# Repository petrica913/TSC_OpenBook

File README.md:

# 📘 OpenBook - EBook Reader with ESP32-C6

## 📊 Block diagram

## 🧠 Detailed Hardware Description

### Microcontroller
- **ESP32-C6-WROOM-1-N8** – Main MCU with WiFi 6 and BLE 5.0 support.
- Manages all components and communication interfaces.

### Power Supply
- **USB-C Connector (J2)** – for powering and charging the device.
- **MCP73831** – LiPo battery charging IC.
- **P-Channel MOSFETs (Q1, Q2)** – for automatic switching between USB and battery power.
- **Varistor and 5.1kΩ resistors** – for overvoltage protection and USB-C detection.

### Display
- **eInk display** controlled via **SPI** interface:
  - Lines: CLK, MOSI, CS, DC (Data/Command), RST (Reset), BUSY (status).
  - Extremely power-efficient – consumes power only during screen refresh.

### User Interface
- Physical buttons for menu control:
  - Left/Right navigation and Select.
  - Connected to GPIOs configured as input, some with pull-up/down resistors.

### Sensors (optional)
- **BME680** – temperature, humidity, pressure, and VOC sensor.
  - Communicates via I2C.
  - Connected to GPIOs with 10kΩ pull-up resistors.

### Other Components
- Resistors, filtering and decoupling capacitors.
- Status LEDs (optional).

## 🔋 Estimated Power Consumption

| Component                                | Estimated Current             |
|------------------------------------------|-------------------------------|
| ESP32-C6 (CPU active, without Wi-Fi)     | ~80–120 mA                    |
| E-Paper (page refresh)                   | ~10–15 mA *(only during refresh)* |
| MicroSD (active access)                  | ~30–60 mA                     |
| RTC DS3231                               | ~0.2 mA                       |
| BME688 Sensor (1Hz)                      | ~3.7 µA                       |
| Fuel Gauge MAX17048 (active)             | ~23 µA                        |
| LDO Regulator (quiescent current)        | ~1 µA                         |
| **Total estimated (without refresh)**    | **~110–130 mA**               |
| **Total during EPD refresh**             | **~140–170 mA**               |

## 🔌 Pin Allocation of ESP32-C6

| Pin Number | GPIO | Function              | Componenta                            | Reason for Use                                   |
|------------|------|------------------------|---------------------------------------|--------------------------------------------------------|
| 3          | EN   | Reset                  | Reset Button                          | Hardware-defined enable pin                            |
| 8          | GPIO0 | SQW/INT               | RTC DS3231SN Interrupt                | Used to wakeup from sleep using an interrupt from RTC  |
| 9          | GPIO1 | 32KHz input           | RTC DS3231SN 32KHz output             | Low power timing source for RTC operations             |
| 27         | GPIO2 | MISO                  | SD Card, E-Paper, NOR Flash           | SPI MISO - receives data from connected peripherals    |
| 28         | GPIO3 | EPD_BUSY              | E-Paper Display busy signal           | Indicates the status of the E-Paper display            |
| 30         | GPIO4 | SD_CS                 | SD Card chip select                   | Selects the SD card on the SPI bus                     |
| 31         | GPIO5 | EPD_DC                | E-Paper Display data/command          | Distinguishes data/command                             |
| 32         | GPIO6 | SCK                   | SD Card, E-Paper, NOR Flash           | SPI clock line                                         |
| 33         | GPIO7 | MOSI                  | SD Card, E-Paper, NOR Flash           | SPI data line                                          |
| 10         | GPIO8 | Pull-up               | Reserved - Unused                     | Left free                                              |
| 13         | GPIO9 | Boot                  | Boot Button                           | Enter flashing mode                                    |
| 14         | GPIO10 | EPD_CS               | E-Paper Display chip select           | Selects E-Paper                                        |
| 15         | GPIO11 | FLASH_CS             | NOR Flash chip select                 | Selects external flash                                 |
| 16         | GPIO12 | USB_D-               | USB Data negative                     | USB data line                                          |
| 17         | GPIO13 | USB_D+               | USB Data positive                     | USB data line                                          |
| 23         | GPIO15 | Navigation           | Change Button                         | Input detection                                        |
| 25         | GPIO16 | TX                   | Test Pad                              | TX                                                     |
| 24         | GPIO17 | RX                   | Test Pad                              | RX                                                     |
| 16         | GPIO18 | RTC_RST              | RTC reset                             | Resets RTC module                                      |
| 17         | GPIO19 | I2C_PW               | BME688 power control                  | Powers I2C modules                                     |
| 18         | GPIO20 | EPD_3V3              | DMG2305UX-7                           | Controls power supply to E-Paper display               |
| 19         | GPIO21 | SDA                  | I2C data (RTC, BME688, Battery Gauge) | I2C data line                                          |
| 20         | GPIO22 | SCL                  | I2C clock (RTC, BME688, Battery Gauge)| I2C clock line                                         |
| 21         | GPIO23 | EPD_RST              | E-Paper Display reset                 | Resets the display                                     |

## 📋 Bill of Materials (BOM)
[The bill of materials can be found here](Manufacturing/BOM_OpenBook.csv)

## 🎬 Video of the OpenBook

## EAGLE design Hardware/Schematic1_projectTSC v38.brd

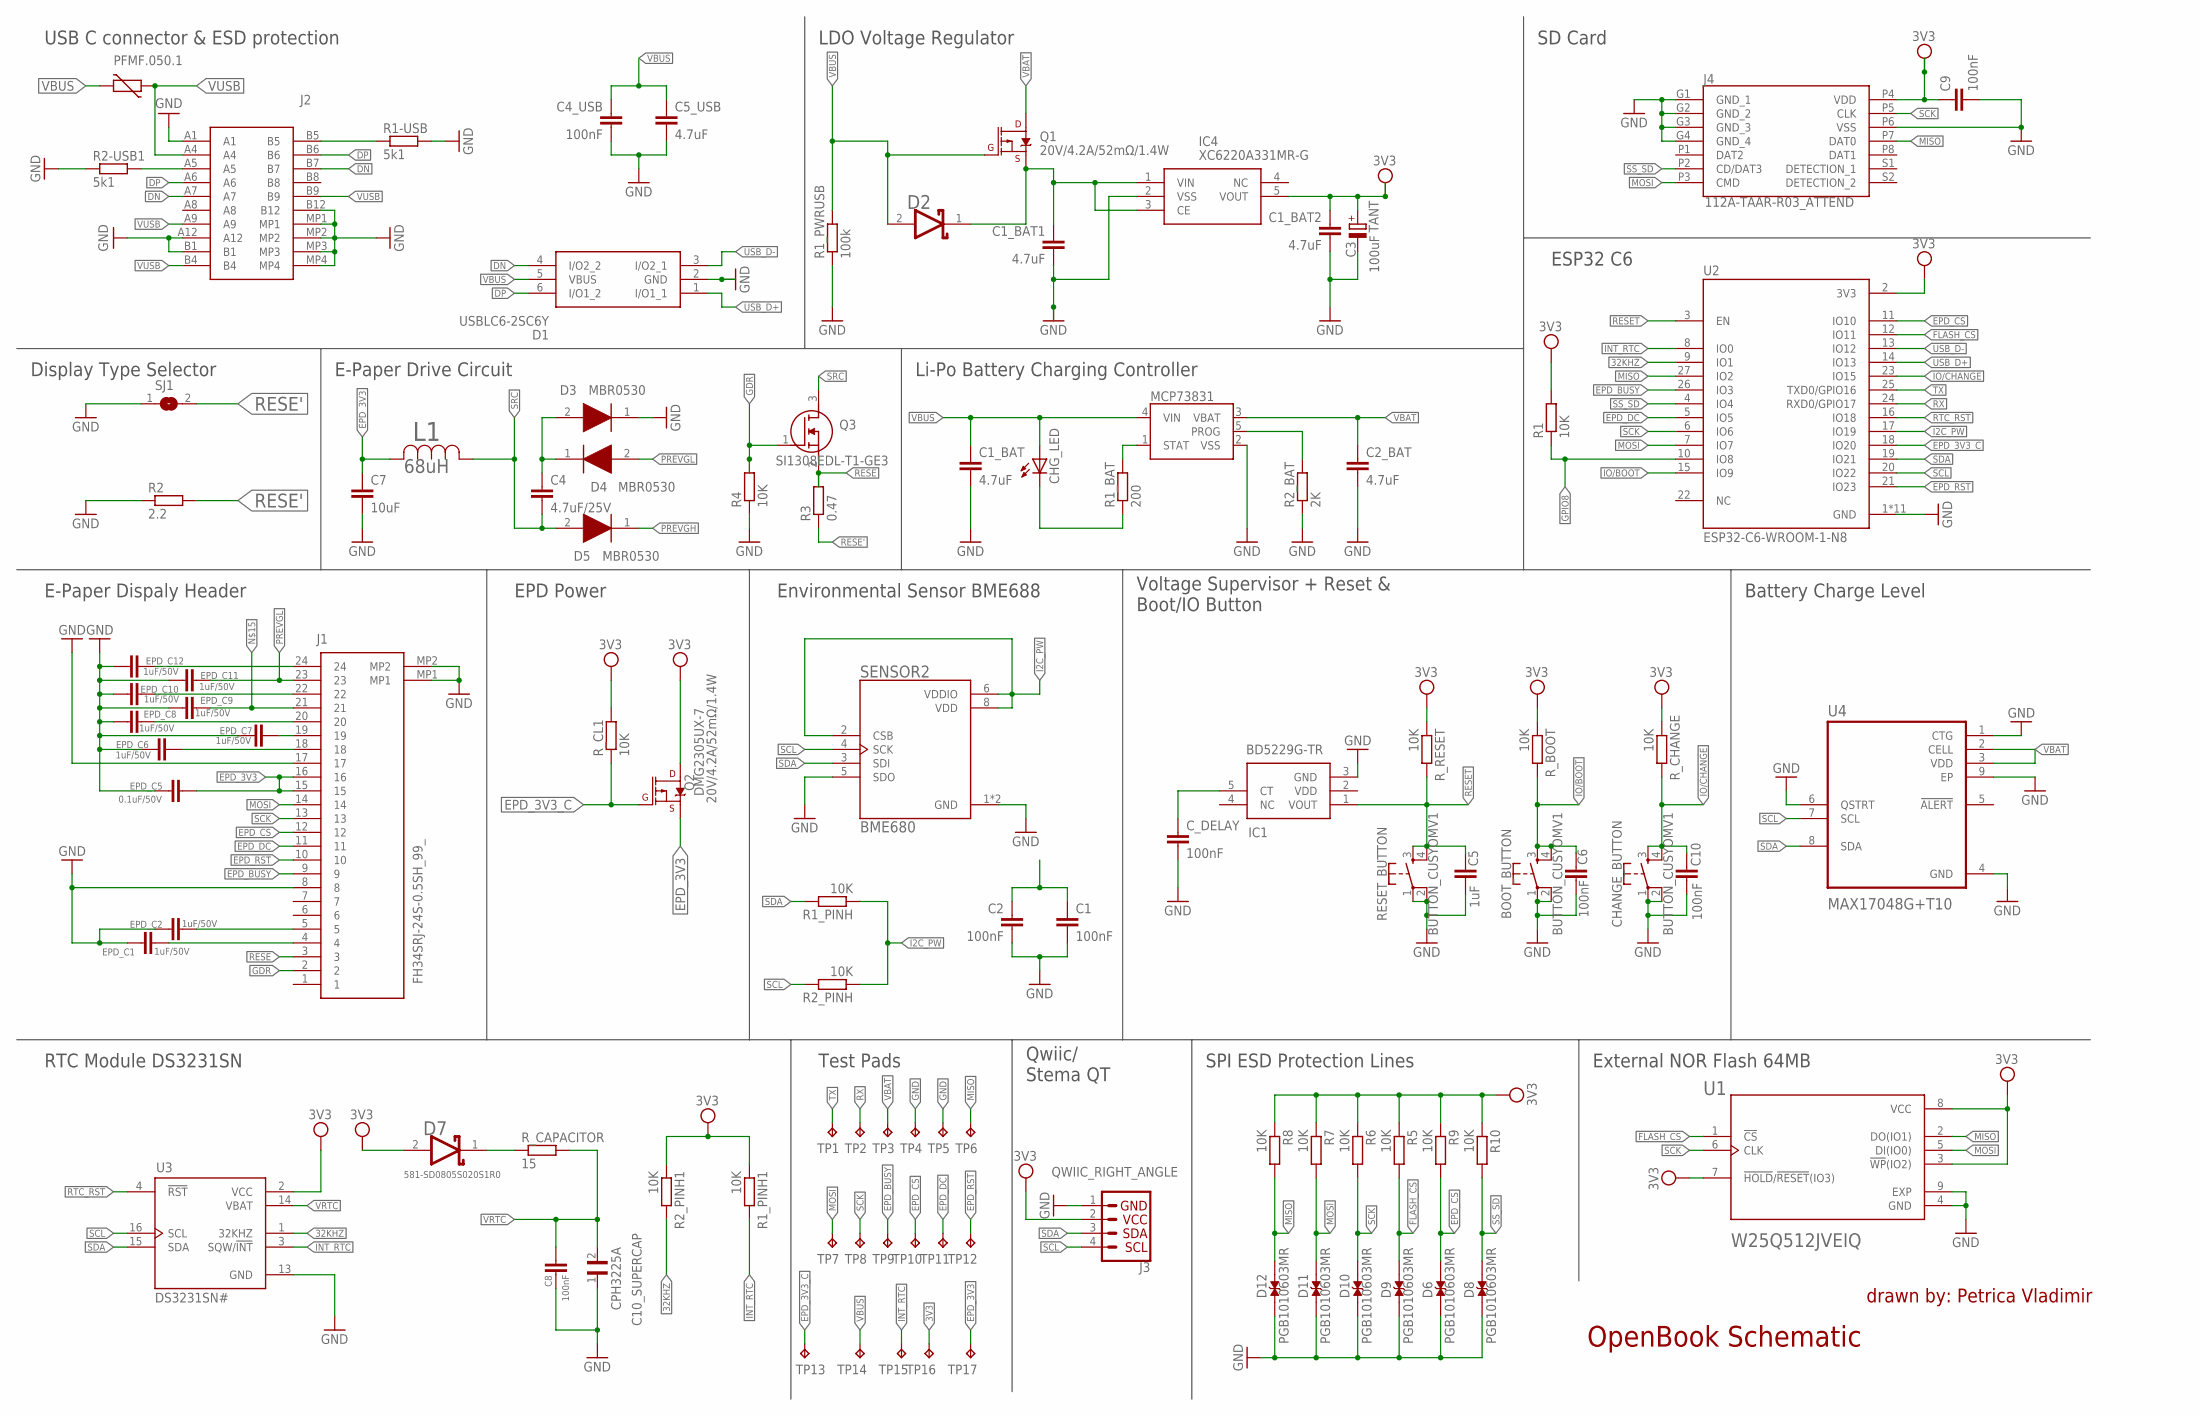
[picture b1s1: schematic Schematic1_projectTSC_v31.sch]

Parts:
BOOT_BUTTON: BUTTON_CUSYOMV1; MYBUTTON
C1, C2, C4_USB, C6, C8, C9, C10: 100nF; EAGLE-LTSPICE_C0402
C1_BAT, C1_BAT1, C1_BAT2, C2_BAT, C5_USB: 4.7uF; EAGLE-LTSPICE_C0402
C3: 100uF; RCL_CT3528
C4: 4.7uF/25V; EAGLE-LTSPICE_C0402
C5: 1uF; EAGLE-LTSPICE_C0402
C7: 10uF; EAGLE-LTSPICE_C0402
C10_SUPERCAP: CPH3225A; CAPCP3225X100N
CHANGE_BUTTON: BUTTON_CUSYOMV1; MYBUTTON
CHG_LED: ADAFRUIT_LEDCHIP-LED0603; ADAFRUIT_CHIP-LED0603
C_DELAY: 100nF; EAGLE-LTSPICE_C0402
D1: USBLC6-2SC6Y; SOT95P280X145-6N
D2, D7: ESP32_WROVER_AVX---SD0805S020S1R0_AVX_SD0805S020S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; ESP32_WROVER_AVX---SD0805S020S1R0_AVX_SD0805S020S1R0_0
D3, D4, D5: MBR0530; SOD3716X135N
D6, D8, D9, D10, D11, D12: PGB1010603MR; DIOC1608X36N
EPD_C1, EPD_C2, EPD_C6, EPD_C7, EPD_C8, EPD_C9, EPD_C10, EPD_C11, EPD_C12: 1uF/50V; EAGLE-LTSPICE_C0402
EPD_C5: 0.1uF/50V; EAGLE-LTSPICE_C0402
IC1: BD5229G-TR; SOT95P280X125-5N
IC4: XC6220A331MR-G; SOT95P280X120-5N
J1: FH34SRJ-24S-0.5SH_99_; FH34SRJ24S05SH99
J2: SAMACSYS_PARTS_USB4110-GF-A; SAMACSYS_PARTS_USB4110GFA
J3: QWIIC_RIGHT_ANGLE; JST04_1MM_RA
J4: 112A-TAAR-R03_ATTEND; 112ATAARR03ATTEND
L1: 744043680IND_4828-WE-TPC_WRE; IND_4828-WE-TPC_WRE; MANUFACTURER_PART_NUMBER 68uH
MCP73831: ESP32_WROVER_SPARKFUN-IC-POWER_MCP73831; ESP32_WROVER_SPARKFUN-IC-POWER_SOT23-5
PFMF.050.1: ESP32C6_VARISTORCN1812; ESP32C6_VARISTOR_CT/CN1812
Q1, Q2: 20V/4.2A/52mΩ/1.4W; ESP32_WROVER_SPARKFUN-DISCRETESEMI_SOT23-3
Q3: SI1308EDL-T1-GE3; SOT65P210X110-3N
R1, R1_PINH, R1_PINH1, R2_PINH, R2_PINH1, R4, R5, R6, R7, R8, R9, R10: 10K; ESP32_WROVER_EAGLE-LTSPICE_R0402
R1-USB, R2-USB1: 5k1; ESP32_WROVER_EAGLE-LTSPICE_R0402
R1_BAT: 200; ESP32_WROVER_EAGLE-LTSPICE_R0402
R1_PWRUSB: 100k; ESP32_WROVER_EAGLE-LTSPICE_R0402
R2: 2.2; ESP32_WROVER_EAGLE-LTSPICE_R0402
R2_BAT: 2K; ESP32_WROVER_EAGLE-LTSPICE_R0402
R3: 0.47; ESP32_WROVER_EAGLE-LTSPICE_R0402
RESET_BUTTON: BUTTON_CUSYOMV1; MYBUTTON
R_BOOT: 10K; ESP32_WROVER_EAGLE-LTSPICE_R0402
R_CAPACITOR: 15; ESP32_WROVER_EAGLE-LTSPICE_R0402
R_CHANGE: 10K; ESP32_WROVER_EAGLE-LTSPICE_R0402
R_CL1: 10K; ESP32_WROVER_EAGLE-LTSPICE_R0402
R_RESET: 10K; ESP32_WROVER_EAGLE-LTSPICE_R0402
SENSOR2: ESP32_WROVER_BME680_BME680; ESP32_WROVER_BME680_PSON80P300X300X100-8N
SJ1: SJ
TP1, TP2, TP3, TP4, TP5, TP6, TP7, TP8, TP9, TP10, TP11, TP12, TP13, TP14, TP15, TP16, TP17: TPTP20R; TP20R
U1: W25Q512JVEIQ; SON127P600X800X80-9N
U2: ESP32-C6-WROOM-1-N8; XCVR_ESP32-C6-WROOM-1-N8
U3: DS3231SN#; SOIC127P1032X265-16N
U4: MAX17048G+T10; SON50P200X200X80-9N

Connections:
3V3: C1_BAT2.1, C3.+, C9.1, D7.2 (ANODE), IC4.5 (VOUT), J3.2, J4.P4 (VDD), Q2.3 (D), R1.2, R1_PINH1.1, R2_PINH1.1, R5.1, R6.1, R7.1, R8.1, R9.1, R10.1, R_BOOT.1, R_CHANGE.1, R_CL1.2, R_RESET.1, TP16.TP, U1.3 (!WP!(IO2)), U1.7 (!HOLD!/!RESET!(IO3)), U1.8 (VCC), U2.2 (3V3), U3.2 (VCC)
32KHZ: R2_PINH1.2, U2.9 (IO1), U3.1 (32KHZ)
DN: D1.4 (I/O2_2), J2.A7, J2.B7
DP: D1.6 (I/O1_2), J2.A6, J2.B6
EPD_3V3_C: Q2.1 (G), R_CL1.1, TP13.TP, U2.18 (IO20)
EPD_BUSY: J1.9, TP9.TP, U2.26 (IO3)
EPD_CS: D6.2, J1.12, R9.2, TP10.TP, U2.11 (IO10)
EPD_DC: J1.11, TP11.TP, U2.5 (IO5)
EPD_RST: J1.10, TP12.TP, U2.21 (IO23)
FLASH_CS: D9.2, R5.2, U1.1 (!CS), U2.12 (IO11)
GDR: J1.2, Q3.1 (G), R4.2
GPIO8: R1.1, U2.10 (IO8)
I2C_PW: R1_PINH.1, R2_PINH.1, SENSOR2.2 (CSB), SENSOR2.6 (VDDIO), SENSOR2.8 (VDD), U2.17 (IO19)
INT_RTC: R1_PINH1.2, TP15.TP, U2.8 (IO0), U3.3 (SQW/!INT)
IO/BOOT: BOOT_BUTTON.3, BOOT_BUTTON.4, C6.1, R_BOOT.2, U2.15 (IO9)
IO/CHANGE: C10.1, CHANGE_BUTTON.3, CHANGE_BUTTON.4, R_CHANGE.2, U2.23 (IO15)
MISO: D12.2, J4.P7 (DAT0), R8.2, TP6.TP, U1.2 (DO(IO1)), U2.27 (IO2)
MOSI: D11.2, J1.14, J4.P3 (CMD), R7.2, TP7.TP, U1.5 (DI(IO0)), U2.7 (IO7)
unnamed: J2.A5, R2-USB1.2
unnamed: J2.B5, R1-USB.1
unnamed: MCP73831.1 (STAT), R1_BAT.2
unnamed: C1_BAT1.1, D2.1 (CATHODE), IC4.1 (VIN), IC4.3 (CE), Q1.2 (S)
unnamed: CHG_LED.C, R1_BAT.1
unnamed: C4.1, D3.2 (A), D4.1 (K)
unnamed: MCP73831.5 (PROG), R2_BAT.2
unnamed: EPD_C2.2, J1.5
unnamed: EPD_C8.2, J1.20
unnamed: EPD_C12.2, J1.24
unnamed: EPD_C1.2, J1.4
unnamed: EPD_C10.2, J1.22
unnamed: C_DELAY.1, IC1.5 (CT)
unnamed: D7.1 (CATHODE), R_CAPACITOR.1
unnamed: EPD_C7.2, J1.19
unnamed: EPD_C6.2, J1.18
PREVGL: D4.2 (A), EPD_C11.2, J1.23
RESE: J1.3, Q3.2 (S), R3.2
RESE': R2.2, R3.1, SJ1.2
RESET: C5.1, IC1.1 (VOUT), RESET_BUTTON.3, RESET_BUTTON.4, R_RESET.2, U2.3 (EN)
RTC_RST: U2.16 (IO18), U3.4 (!RST)
RX: TP2.TP, U2.24 (RXD0/GPIO17)
SCK: D10.2, J1.13, J4.P5 (CLK), R6.2, TP8.TP, U1.6 (CLK), U2.6 (IO6)
SCL: J3.4, R2_PINH.2, SENSOR2.4 (SCK), U2.20 (IO22), U3.16 (SCL), U4.7 (SCL)
SDA: J3.3, R1_PINH.2, SENSOR2.3 (SDI), U2.19 (IO21), U3.15 (SDA), U4.8 (SDA)
SRC: C4.2, D5.2 (A), L1.1, Q3.3 (D)
SS_SD: D8.2, J4.P2 (CD/DAT3), R10.2, U2.4 (IO4)
TX: TP1.TP, U2.25 (TXD0/GPIO16)
USB_D+: D1.1 (I/O1_1), U2.14 (IO13)
USB_D-: D1.3 (I/O2_1), U2.13 (IO12)
VBAT: C2_BAT.1, MCP73831.3 (VBAT), Q1.3 (D), TP3.TP, U4.2 (CELL), U4.3 (VDD)
VBUS1: C1.1, C2.1
VRTC: C8.2, C10_SUPERCAP.2, R_CAPACITOR.2, U3.14 (VBAT)

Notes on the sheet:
USB C connector & ESD protection
SD Card
LDO Voltage Regulator
Display Type Selector
E-Paper Drive Circuit
Li-Po Battery Charging Controller
ESP32 C6
E-Paper Dispaly Header
EPD Power
Environmental Sensor BME688
Voltage Supervisor + Reset & Boot/IO Button
Battery Charge Level
RTC Module DS3231SN
Test Pads
Qwiic/ Stema QT
SPI ESD Protection Lines
External NOR Flash 64MB
OpenBook Schematic
drawn by: Petrica Vladimir

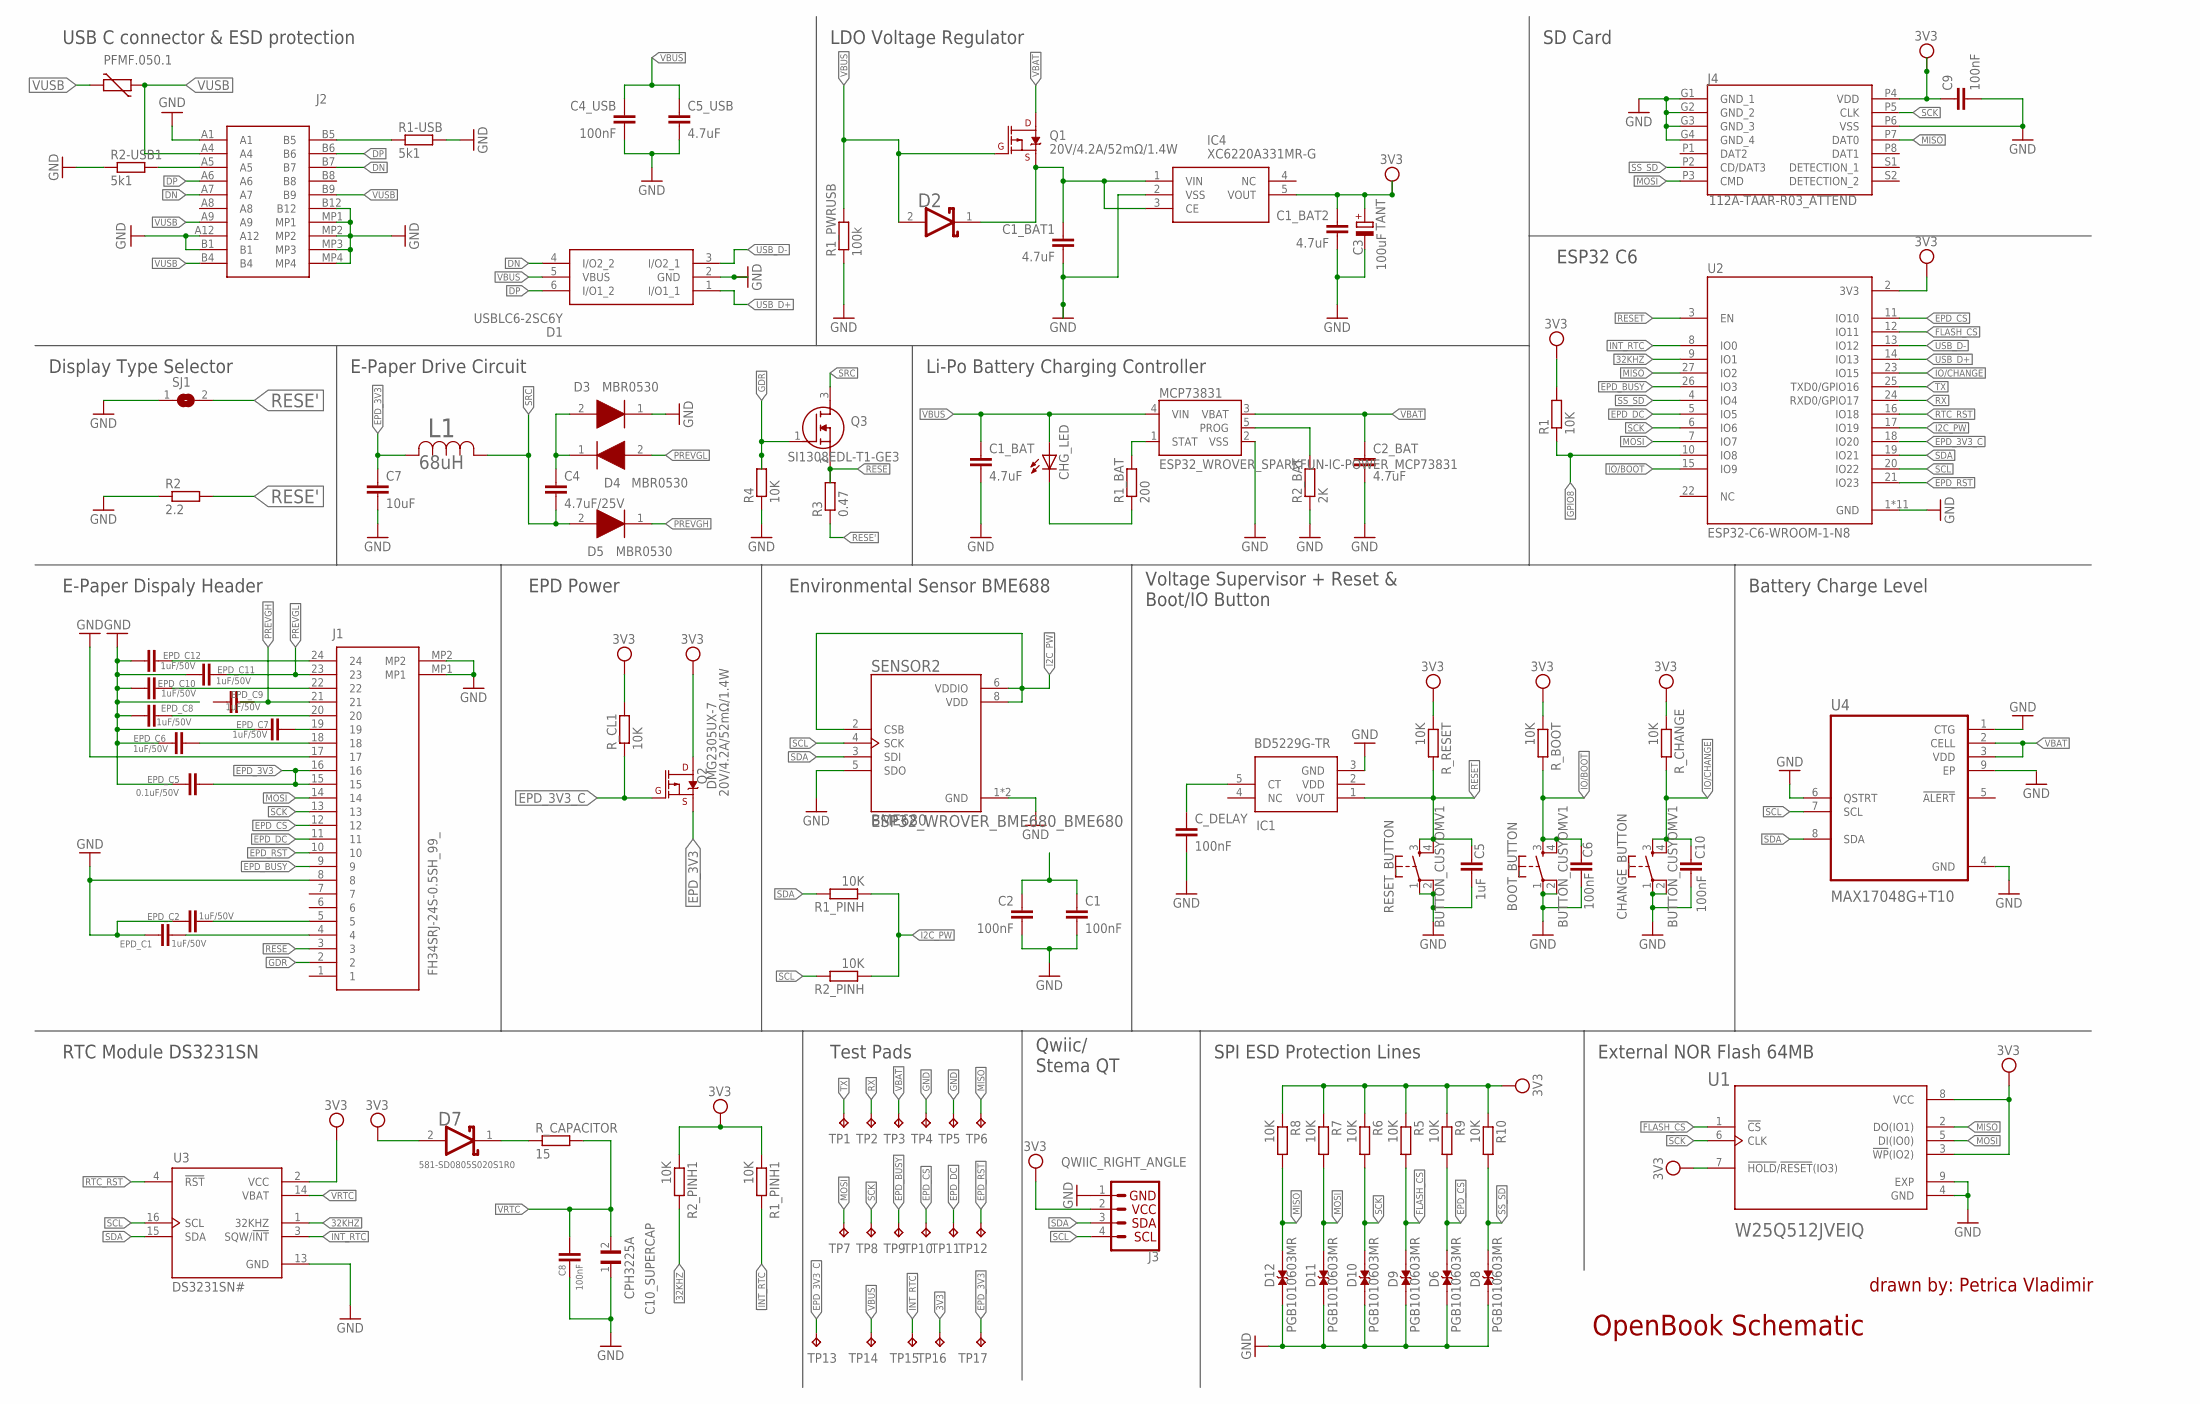
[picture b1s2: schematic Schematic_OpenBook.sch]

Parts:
BOOT_BUTTON: BUTTON_CUSYOMV1; MYBUTTON
C1, C2, C4_USB, C6, C8, C9, C10: 100nF; EAGLE-LTSPICE_C0402
C1_BAT, C1_BAT1, C1_BAT2, C2_BAT, C5_USB: 4.7uF; EAGLE-LTSPICE_C0402
C3: 100uF; RCL_CT3528
C4: 4.7uF/25V; EAGLE-LTSPICE_C0402
C5: 1uF; EAGLE-LTSPICE_C0402
C7: 10uF; EAGLE-LTSPICE_C0402
C10_SUPERCAP: CPH3225A; CAPCP3225X100N
CHANGE_BUTTON: BUTTON_CUSYOMV1; MYBUTTON
CHG_LED: ADAFRUIT_LEDCHIP-LED0603; ADAFRUIT_CHIP-LED0603
C_DELAY: 100nF; EAGLE-LTSPICE_C0402
D1: USBLC6-2SC6Y; SOT95P280X145-6N
D2, D7: ESP32_WROVER_AVX---SD0805S020S1R0_AVX_SD0805S020S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; ESP32_WROVER_AVX---SD0805S020S1R0_AVX_SD0805S020S1R0_0
D3, D4, D5: MBR0530; SOD3716X135N
D6, D8, D9, D10, D11, D12: PGB1010603MR; DIOC1608X36N
EPD_C1, EPD_C2, EPD_C6, EPD_C7, EPD_C8, EPD_C9, EPD_C10, EPD_C11, EPD_C12: 1uF/50V; EAGLE-LTSPICE_C0402
EPD_C5: 0.1uF/50V; EAGLE-LTSPICE_C0402
IC1: BD5229G-TR; SOT95P280X125-5N
IC4: XC6220A331MR-G; SOT95P280X120-5N
J1: FH34SRJ-24S-0.5SH_99_; FH34SRJ24S05SH99
J2: SAMACSYS_PARTS_USB4110-GF-A; SAMACSYS_PARTS_USB4110GFA
J3: QWIIC_RIGHT_ANGLE; JST04_1MM_RA
J4: 112A-TAAR-R03_ATTEND; 112ATAARR03ATTEND
L1: 744043680IND_4828-WE-TPC_WRE; IND_4828-WE-TPC_WRE; MANUFACTURER_PART_NUMBER 68uH
MCP73831: ESP32_WROVER_SPARKFUN-IC-POWER_MCP73831; ESP32_WROVER_SPARKFUN-IC-POWER_SOT23-5
PFMF.050.1: ESP32C6_VARISTORCN1812; ESP32C6_VARISTOR_CT/CN1812
Q1, Q2: 20V/4.2A/52mΩ/1.4W; ESP32_WROVER_SPARKFUN-DISCRETESEMI_SOT23-3
Q3: SI1308EDL-T1-GE3; SOT65P210X110-3N
R1, R1_PINH, R1_PINH1, R2_PINH, R2_PINH1, R4, R5, R6, R7, R8, R9, R10: 10K; ESP32_WROVER_EAGLE-LTSPICE_R0402
R1-USB, R2-USB1: 5k1; ESP32_WROVER_EAGLE-LTSPICE_R0402
R1_BAT: 200; ESP32_WROVER_EAGLE-LTSPICE_R0402
R1_PWRUSB: 100k; ESP32_WROVER_EAGLE-LTSPICE_R0402
R2: 2.2; ESP32_WROVER_EAGLE-LTSPICE_R0402
R2_BAT: 2K; ESP32_WROVER_EAGLE-LTSPICE_R0402
R3: 0.47; ESP32_WROVER_EAGLE-LTSPICE_R0402
RESET_BUTTON: BUTTON_CUSYOMV1; MYBUTTON
R_BOOT: 10K; ESP32_WROVER_EAGLE-LTSPICE_R0402
R_CAPACITOR: 15; ESP32_WROVER_EAGLE-LTSPICE_R0402
R_CHANGE: 10K; ESP32_WROVER_EAGLE-LTSPICE_R0402
R_CL1: 10K; ESP32_WROVER_EAGLE-LTSPICE_R0402
R_RESET: 10K; ESP32_WROVER_EAGLE-LTSPICE_R0402
SENSOR2: ESP32_WROVER_BME680_BME680; ESP32_WROVER_BME680_PSON80P300X300X100-8N
SJ1: SJ
TP1, TP2, TP3, TP4, TP5, TP6, TP7, TP8, TP9, TP10, TP11, TP12, TP13, TP14, TP15, TP16, TP17: TPTP20R; TP20R
U1: W25Q512JVEIQ; SON127P600X800X80-9N
U2: ESP32-C6-WROOM-1-N8; XCVR_ESP32-C6-WROOM-1-N8
U3: DS3231SN#; SOIC127P1032X265-16N
U4: MAX17048G+T10; SON50P200X200X80-9N

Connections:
3V3: C1_BAT2.1, C3.+, C9.1, D7.2 (ANODE), IC4.5 (VOUT), J3.2, J4.P4 (VDD), Q2.3 (D), R1.2, R1_PINH1.1, R2_PINH1.1, R5.1, R6.1, R7.1, R8.1, R9.1, R10.1, R_BOOT.1, R_CHANGE.1, R_CL1.2, R_RESET.1, TP16.TP, U1.3 (!WP!(IO2)), U1.7 (!HOLD!/!RESET!(IO3)), U1.8 (VCC), U2.2 (3V3), U3.2 (VCC)
32KHZ: R2_PINH1.2, U2.9 (IO1), U3.1 (32KHZ)
DN: D1.4 (I/O2_2), J2.A7, J2.B7
DP: D1.6 (I/O1_2), J2.A6, J2.B6
EPD_3V3_C: Q2.1 (G), R_CL1.1, TP13.TP, U2.18 (IO20)
EPD_BUSY: J1.9, TP9.TP, U2.26 (IO3)
EPD_CS: D6.2, J1.12, R9.2, TP10.TP, U2.11 (IO10)
EPD_DC: J1.11, TP11.TP, U2.5 (IO5)
EPD_RST: J1.10, TP12.TP, U2.21 (IO23)
FLASH_CS: D9.2, R5.2, U1.1 (!CS), U2.12 (IO11)
GDR: J1.2, Q3.1 (G), R4.2
GPIO8: R1.1, U2.10 (IO8)
I2C_PW: R1_PINH.1, R2_PINH.1, SENSOR2.2 (CSB), SENSOR2.6 (VDDIO), SENSOR2.8 (VDD), U2.17 (IO19)
INT_RTC: R1_PINH1.2, TP15.TP, U2.8 (IO0), U3.3 (SQW/!INT)
IO/BOOT: BOOT_BUTTON.3, BOOT_BUTTON.4, C6.1, R_BOOT.2, U2.15 (IO9)
IO/CHANGE: C10.1, CHANGE_BUTTON.3, CHANGE_BUTTON.4, R_CHANGE.2, U2.23 (IO15)
MISO: D12.2, J4.P7 (DAT0), R8.2, TP6.TP, U1.2 (DO(IO1)), U2.27 (IO2)
MOSI: D11.2, J1.14, J4.P3 (CMD), R7.2, TP7.TP, U1.5 (DI(IO0)), U2.7 (IO7)
unnamed: J2.A5, R2-USB1.2
unnamed: J2.B5, R1-USB.1
unnamed: MCP73831.1 (STAT), R1_BAT.2
unnamed: C1_BAT1.1, D2.1 (CATHODE), IC4.1 (VIN), IC4.3 (CE), Q1.2 (S)
unnamed: CHG_LED.C, R1_BAT.1
unnamed: C4.1, D3.2 (A), D4.1 (K)
unnamed: MCP73831.5 (PROG), R2_BAT.2
unnamed: EPD_C2.2, J1.5
unnamed: EPD_C8.2, J1.20
unnamed: EPD_C12.2, J1.24
unnamed: EPD_C1.2, J1.4
unnamed: EPD_C10.2, J1.22
unnamed: C_DELAY.1, IC1.5 (CT)
unnamed: D7.1 (CATHODE), R_CAPACITOR.1
unnamed: EPD_C7.2, J1.19
unnamed: EPD_C6.2, J1.18
PREVGL: D4.2 (A), EPD_C11.2, J1.23
RESE: J1.3, Q3.2 (S), R3.2
RESE': R2.2, R3.1, SJ1.2
RESET: C5.1, IC1.1 (VOUT), RESET_BUTTON.3, RESET_BUTTON.4, R_RESET.2, U2.3 (EN)
RTC_RST: U2.16 (IO18), U3.4 (!RST)
RX: TP2.TP, U2.24 (RXD0/GPIO17)
SCK: D10.2, J1.13, J4.P5 (CLK), R6.2, TP8.TP, U1.6 (CLK), U2.6 (IO6)
SCL: J3.4, R2_PINH.2, SENSOR2.4 (SCK), U2.20 (IO22), U3.16 (SCL), U4.7 (SCL)
SDA: J3.3, R1_PINH.2, SENSOR2.3 (SDI), U2.19 (IO21), U3.15 (SDA), U4.8 (SDA)
SRC: C4.2, D5.2 (A), L1.1, Q3.3 (D)
SS_SD: D8.2, J4.P2 (CD/DAT3), R10.2, U2.4 (IO4)
TX: TP1.TP, U2.25 (TXD0/GPIO16)
USB_D+: D1.1 (I/O1_1), U2.14 (IO13)
USB_D-: D1.3 (I/O2_1), U2.13 (IO12)
VBAT: C2_BAT.1, MCP73831.3 (VBAT), Q1.3 (D), TP3.TP, U4.2 (CELL), U4.3 (VDD)
VBUS1: C1.1, C2.1
VRTC: C8.2, C10_SUPERCAP.2, R_CAPACITOR.2, U3.14 (VBAT)

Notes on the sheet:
USB C connector & ESD protection
SD Card
LDO Voltage Regulator
Display Type Selector
E-Paper Drive Circuit
Li-Po Battery Charging Controller
ESP32 C6
E-Paper Dispaly Header
EPD Power
Environmental Sensor BME688
Voltage Supervisor + Reset & Boot/IO Button
Battery Charge Level
RTC Module DS3231SN
Test Pads
Qwiic/ Stema QT
SPI ESD Protection Lines
External NOR Flash 64MB
OpenBook Schematic
drawn by: Petrica Vladimir

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
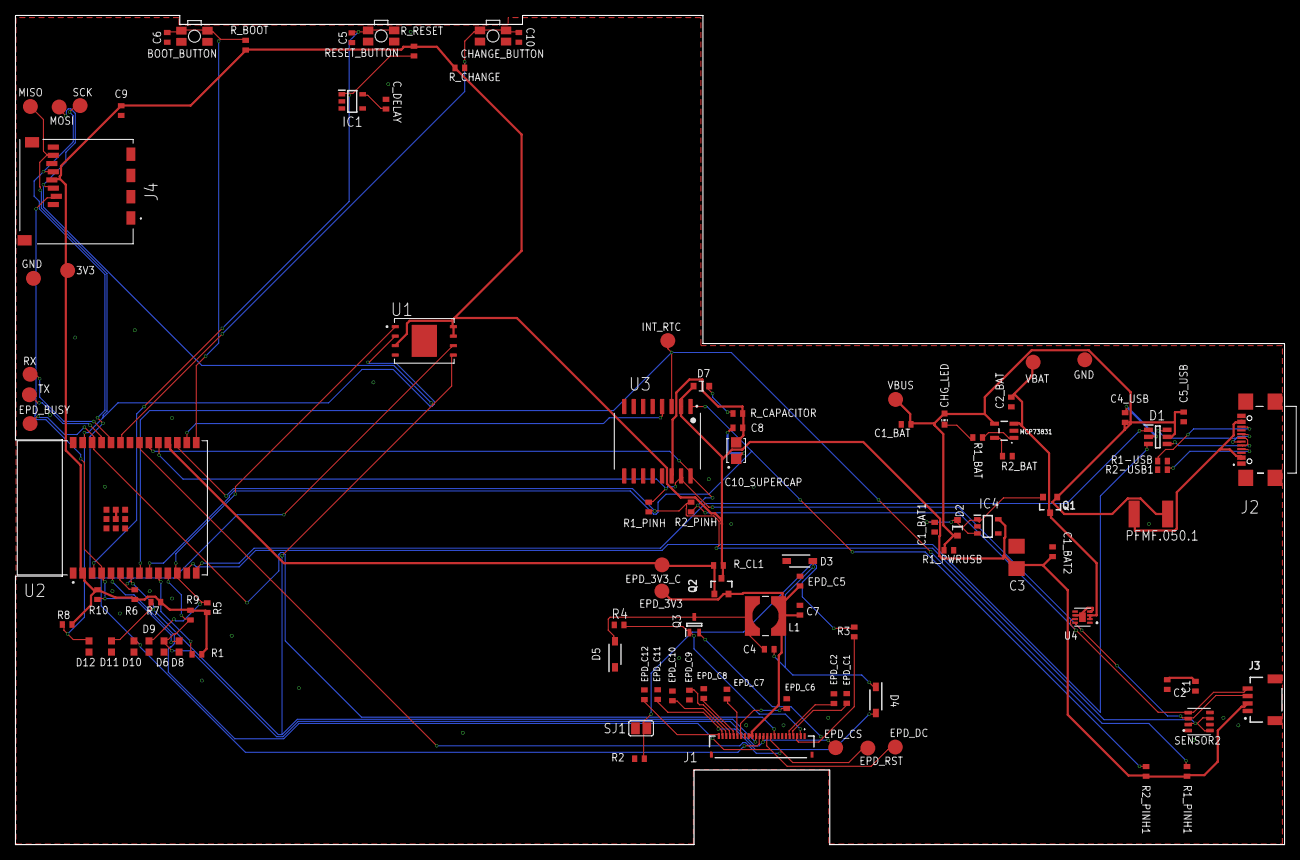
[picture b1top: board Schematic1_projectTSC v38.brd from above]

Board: 2 copper layers, 170.2 x 111.2 mm, 103 parts (0 on the bottom side), 56 nets.

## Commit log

2025-04-06 Rename ESP 32.png to ESP_32.png
2025-04-06 Rename OpenBook video.avi to OpenBook_video.avi
2025-04-06 added .f3z file
2025-04-14 final

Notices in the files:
parts and their libraries:
COPYRIGHT: Copyright (C) 2024 Ultra Librarian. All rights reserved.
